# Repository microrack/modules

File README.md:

# Modules

MICRORACK modules are compact synthesizer building blocks following the [MICRORACK Specification](https://specs.microrack.org/).

> **Open Platform**
>
> Any enthusiast or brand can create and distribute compatible modules — as open source projects or as closed source designs.

## Generators

- [**oscillator**](mod-vco/) - Voltage Controlled Oscillator with LFO mode
- [**noise + s&h**](mod-noise/) - Noise Generator with Sample/Track & Hold
- [**envelope**](mod-env/) - Envelope Generator
- [**sequencer**](mod-seq/) - 4-Step Sequencer

## Sound Processing

- [**filter**](mod-vcf/) - Voltage Controlled Filter
- [**delay**](mod-delay/) - Wild  PT Delay
- [**equalizer**](mod-eq/) - 3 Line Equalizer
- [**compressor**](mod-comp/) - Compressor wit Sidechain
- [**saturator**](mod-sat/) - Saturator / Distortion
- [**lowpass gate**](mod-lpg/) - Low Pass Gate

## Utilities

- [**vca mixer**](mod-vca/) - VCA Mixer
- [**counter**](mod-clk/) - Clock Counter
- [**stylo**](mod-key/) - Stylus Keyboard

## I/O & MIDI

- [**input 6.3**](mod-in-63/) - 6.3mm jack Input
- [**output 3.5**](mod-out-35/) - 3.5mm jack Output
- [**output 6.3**](mod-out-63/) - 6.3mm jack Output
- [**midi→cv**](mod-midi/) - MIDI-CV Interface wi Osciloscope mode
- [**jacket 3.5**](mod-jacket/) - 3.5mm Jacks for Eurorack and more

## Power & Chassis

- [**power**](mod-pwr/) - Power Module
- [**rack chassis**](mod-chassis/) - Eurorack/Standalone Chassis

## Additional Resources

> **Source Repository**
>
> [github.com/microrack/modules](https://github.com/microrack/modules)

- [Documentation](https://docs.microrack.org) - User guides and documentation
- [Specification](https://specs.microrack.org) - Technical specifications
- [Forum](https://forum.microrack.org) - Community discussions

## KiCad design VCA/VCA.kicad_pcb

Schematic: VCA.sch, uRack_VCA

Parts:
C1, C2: 0.1 uF; c0603
J1: Output; pls1x03
J2: Input; pls1x03
J3: Env; pls1x03
J4, J5, J6, J7, J8, J9, J10, J11, J12: Conn_01x05_Male; pls1x05
Q1, Q2, Q3, Q4: BC817; SOT-23
Q5: BC807; SOT-23
R1, R5, R7, R10, R11, R16, R18, R19: 100K; r0603
R2, R3, R9, R17: 24K; r0603
R4, R6, R8, R15: 100R; r0603
R12, R13, R14, R20, R21, R22: 1K; r0603
RV1, RV2: 10K; R0904N
U1: LM324; soic-14

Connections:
+5V: C1.2, J4.1, J4.2, J4.3, J4.4, J4.5, J5.1, J5.2, J5.3, J5.4, J5.5, J6.1, J6.2, J6.3, J6.4, J6.5, R2.1, R3.1, U1.4 (V+)
-5V: C2.1, J9.1, J9.2, J9.3, J9.4, J9.5, J11.1, J11.2, J11.3, J11.4, J11.5, J12.1, J12.2, J12.3, J12.4, J12.5, Q3.2 (E), Q4.2 (E), U1.11 (V-)
/ENV_1: J3.1, R16.2, R20.1
/ENV_2: J3.2, R18.2, R21.1
/ENV_3: J3.3, R19.2, R22.1
/IN_2: J2.2, R7.2, R13.1
/IN_3: J2.3, R10.2, R12.1
GNDREF: C1.1, C2.2, J7.1, J7.2, J7.3, J7.4, J7.5, J8.1, J8.2, J8.3, J8.4, J8.5, J10.1, J10.2, J10.3, J10.4, J10.5, Q2.1 (B), Q5.1 (B), R11.2, R12.2, R13.2, R14.2, R15.2, R20.2, R21.2, R22.2, RV1.1, RV2.1
unnamed: J1.1, R4.1
unnamed: J1.2, R6.1
unnamed: J1.3, R8.1
unnamed: J2.1, R5.2, R14.1
unnamed: Q1.1 (B), R9.1, R15.1
unnamed: Q1.2 (E), Q2.2 (E), Q3.3 (C)
unnamed: Q1.3 (C), R1.2, R2.2, U1.6 (-)
unnamed: Q2.3 (C), R3.2, R11.1, U1.5 (+)
unnamed: Q3.1 (B), Q4.1 (B), Q4.3 (C), Q5.3 (C)
unnamed: Q5.2 (E), R17.1
unnamed: R1.1, R4.2, R6.2, R8.2, U1.7
unnamed: R9.2, RV1.3, U1.1
unnamed: R5.1, R7.1, R10.1, U1.3 (+)
unnamed: R16.1, R18.1, R19.1, U1.10 (+)
unnamed: R17.2, RV2.3, U1.8
unnamed: RV1.2, U1.2 (-)
unnamed: RV2.2, U1.9 (-)

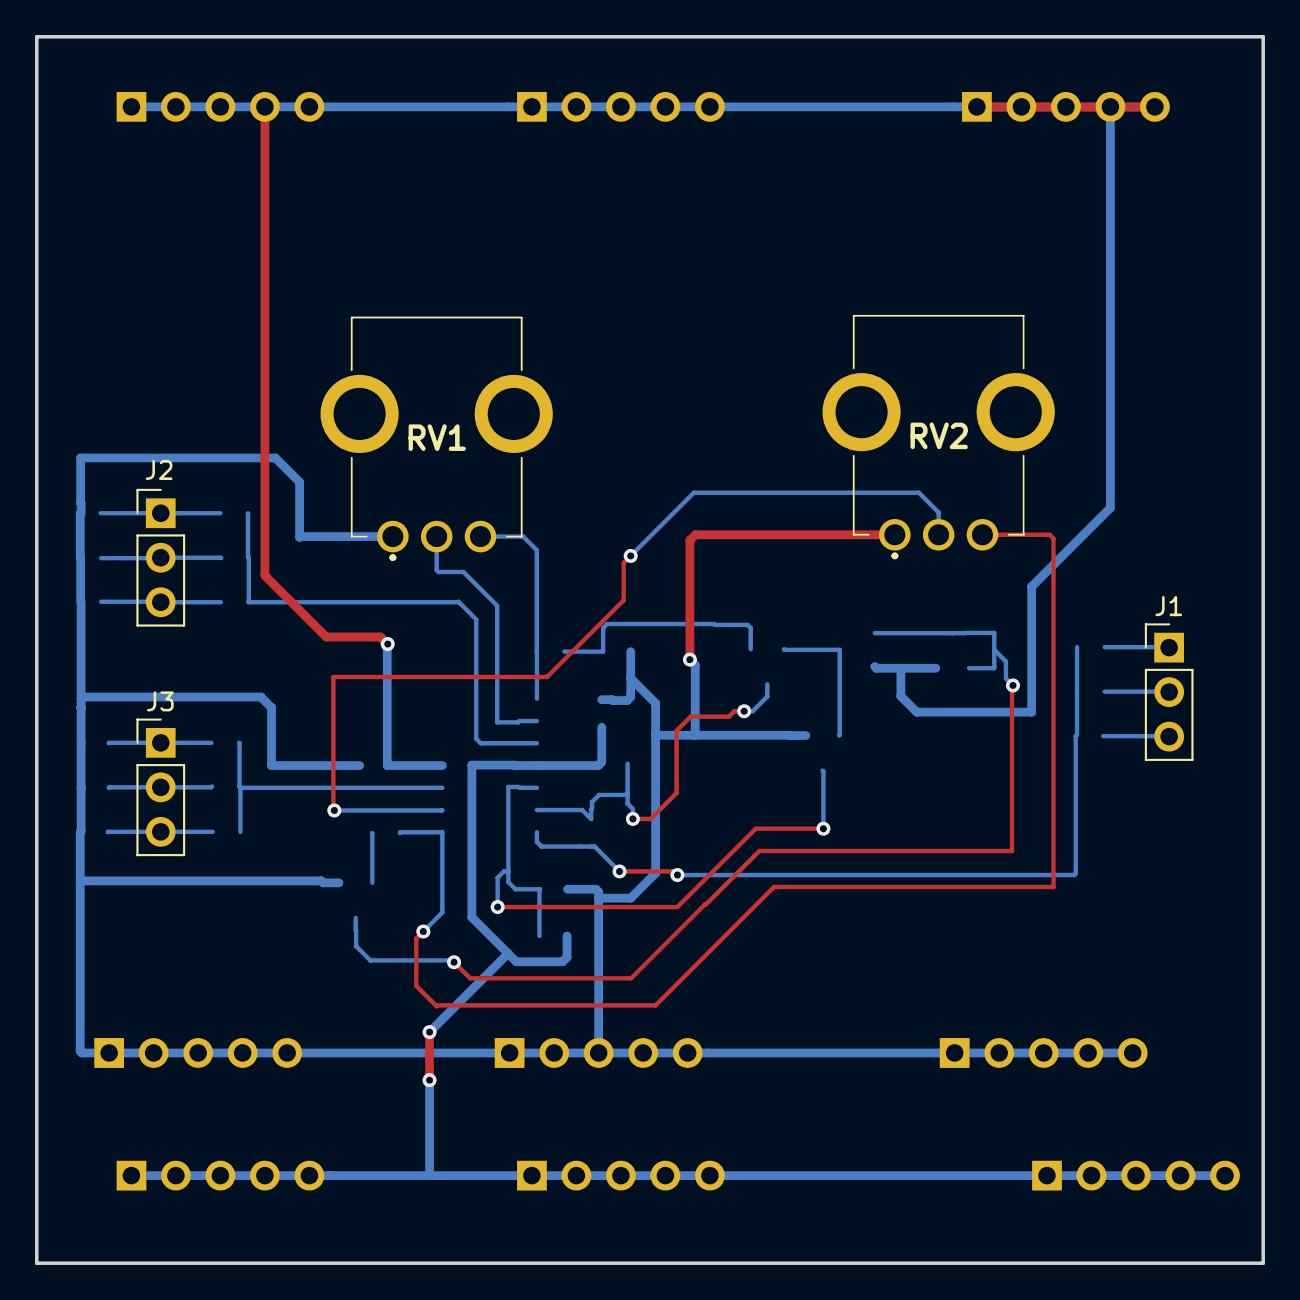
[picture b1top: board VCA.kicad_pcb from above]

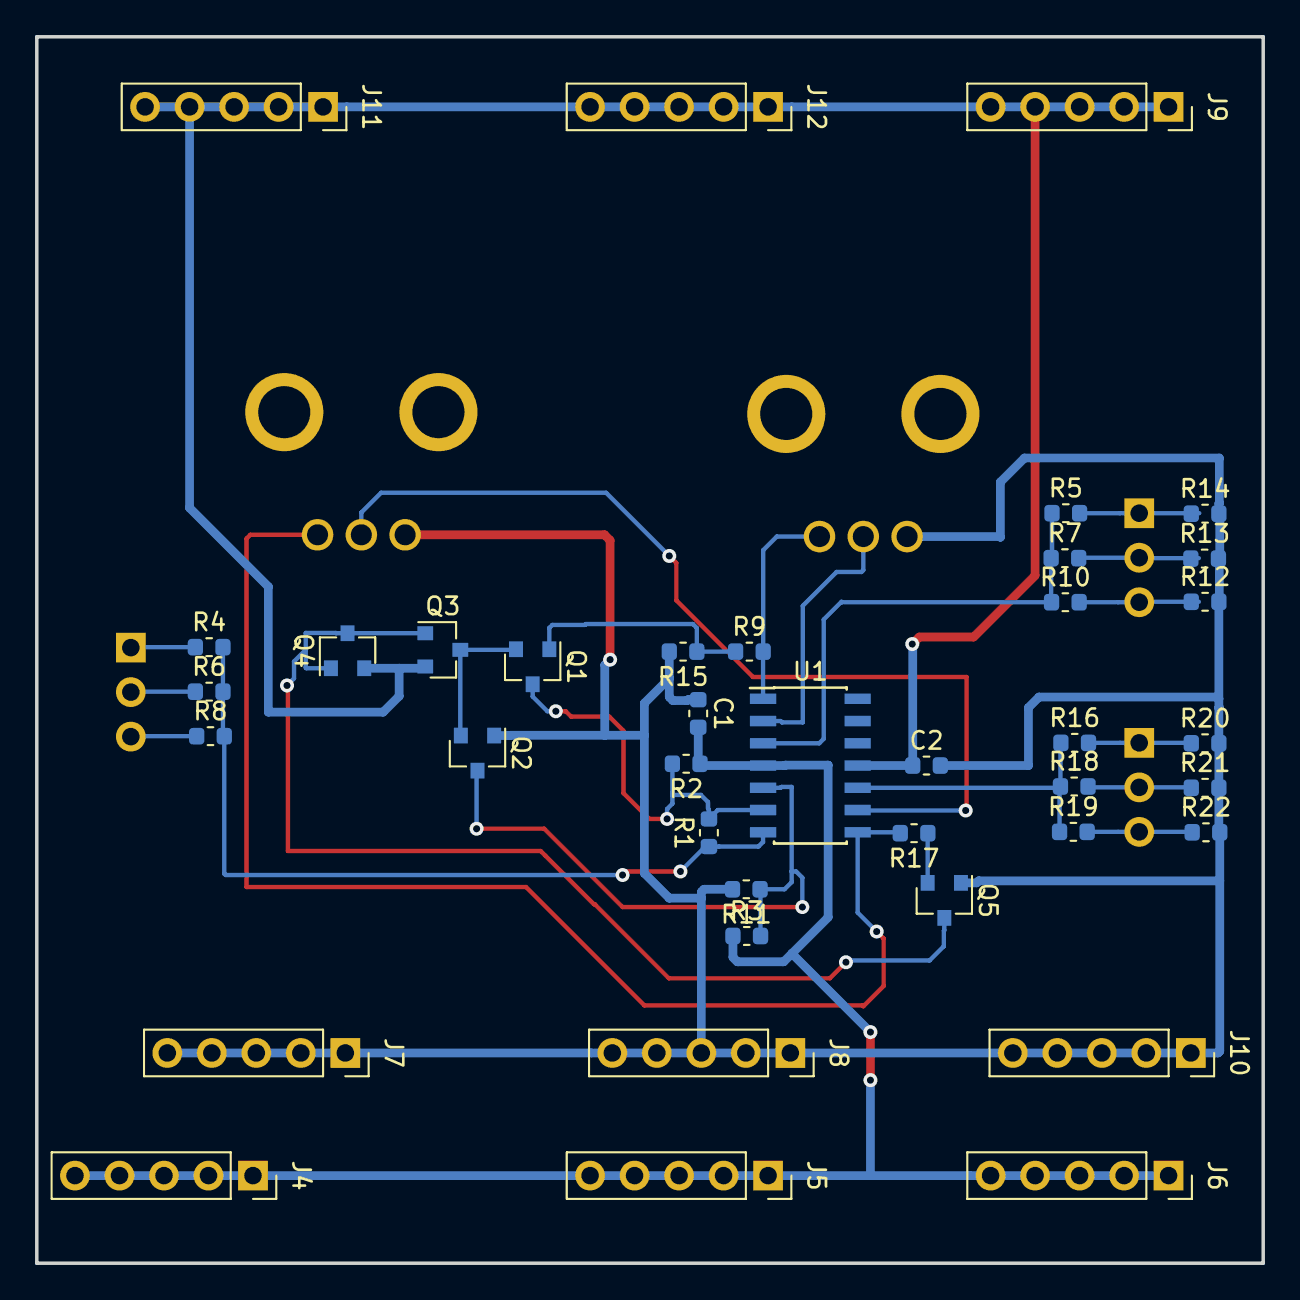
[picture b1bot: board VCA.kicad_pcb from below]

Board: 2 copper layers, 70.0 x 70.0 mm, 44 parts (39 on the bottom side), 25 nets.

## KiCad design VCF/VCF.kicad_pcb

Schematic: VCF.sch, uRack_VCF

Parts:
C1, C2, C3, C4: 0.1 uF; c0603
D1: D; d0603
J1, J2, J4, J5, J6, J7, J8, J10, J12: Conn_01x05_Male; pls1x05
J3: Env; pls1x02
J9: Output; pls1x03
J11: Input; pls1x02
R1, R2, R4, R10, R11: 10K; r0603
R3, R5, R6, R9, R16, R18: 100K; r0603
R7, R8, R19, R20: 1K; r0603
R12, R14, R17: 100R; r0603
R13, R15: 24K; r0603
RV1, RV2, RV3: 10K; R0904N
U1: LM324A; soic-14

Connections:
+5V: C1.2, J1.1, J1.2, J1.3, J1.4, J1.5, J2.1, J2.2, J2.3, J2.4, J2.5, J4.1, J4.2, J4.3, J4.4, J4.5, RV2.1, U1.4 (V+)
-5V: C2.2, J8.1, J8.2, J8.3, J8.4, J8.5, J10.1, J10.2, J10.3, J10.4, J10.5, J12.1, J12.2, J12.3, J12.4, J12.5, RV2.3, U1.11 (V-)
/ENV_2: J3.1, J3.2, R3.2, R5.2, R7.1, R8.1
/IN_2: J11.2, R18.2, R20.1
/OUT_1: J9.1, R12.1
/OUT_2: J9.2, R14.1
GNDREF: C1.1, C2.1, D1.1 (K), J5.1, J5.2, J5.3, J5.4, J5.5, J6.1, J6.2, J6.3, J6.4, J6.5, J7.1, J7.2, J7.3, J7.4, J7.5, R1.2, R7.2, R8.2, R10.2, R19.2, R20.2, RV1.1, U1.12 (+)
unnamed: C3.1, C4.2, D1.2 (A), R4.1
unnamed: C3.2, R13.2, R15.1, U1.13 (-)
unnamed: C4.1, RV3.1
unnamed: J9.3, R17.1
unnamed: J11.1, R16.2, R19.1
unnamed: R1.1, R2.2, U1.6 (-)
unnamed: R2.1, R4.2, U1.7
unnamed: R3.1, R5.1, U1.3 (+)
unnamed: R6.1, R9.1, U1.5 (+)
unnamed: R6.2, RV1.3, U1.1
unnamed: R9.2, RV2.2
unnamed: R10.1, R11.2, U1.9 (-)
unnamed: R11.1, R15.2, U1.8
unnamed: R12.2, R13.1, R14.2, R17.2, RV3.2, RV3.3, U1.14
unnamed: R16.1, R18.1, U1.10 (+)
unnamed: RV1.2, U1.2 (-)

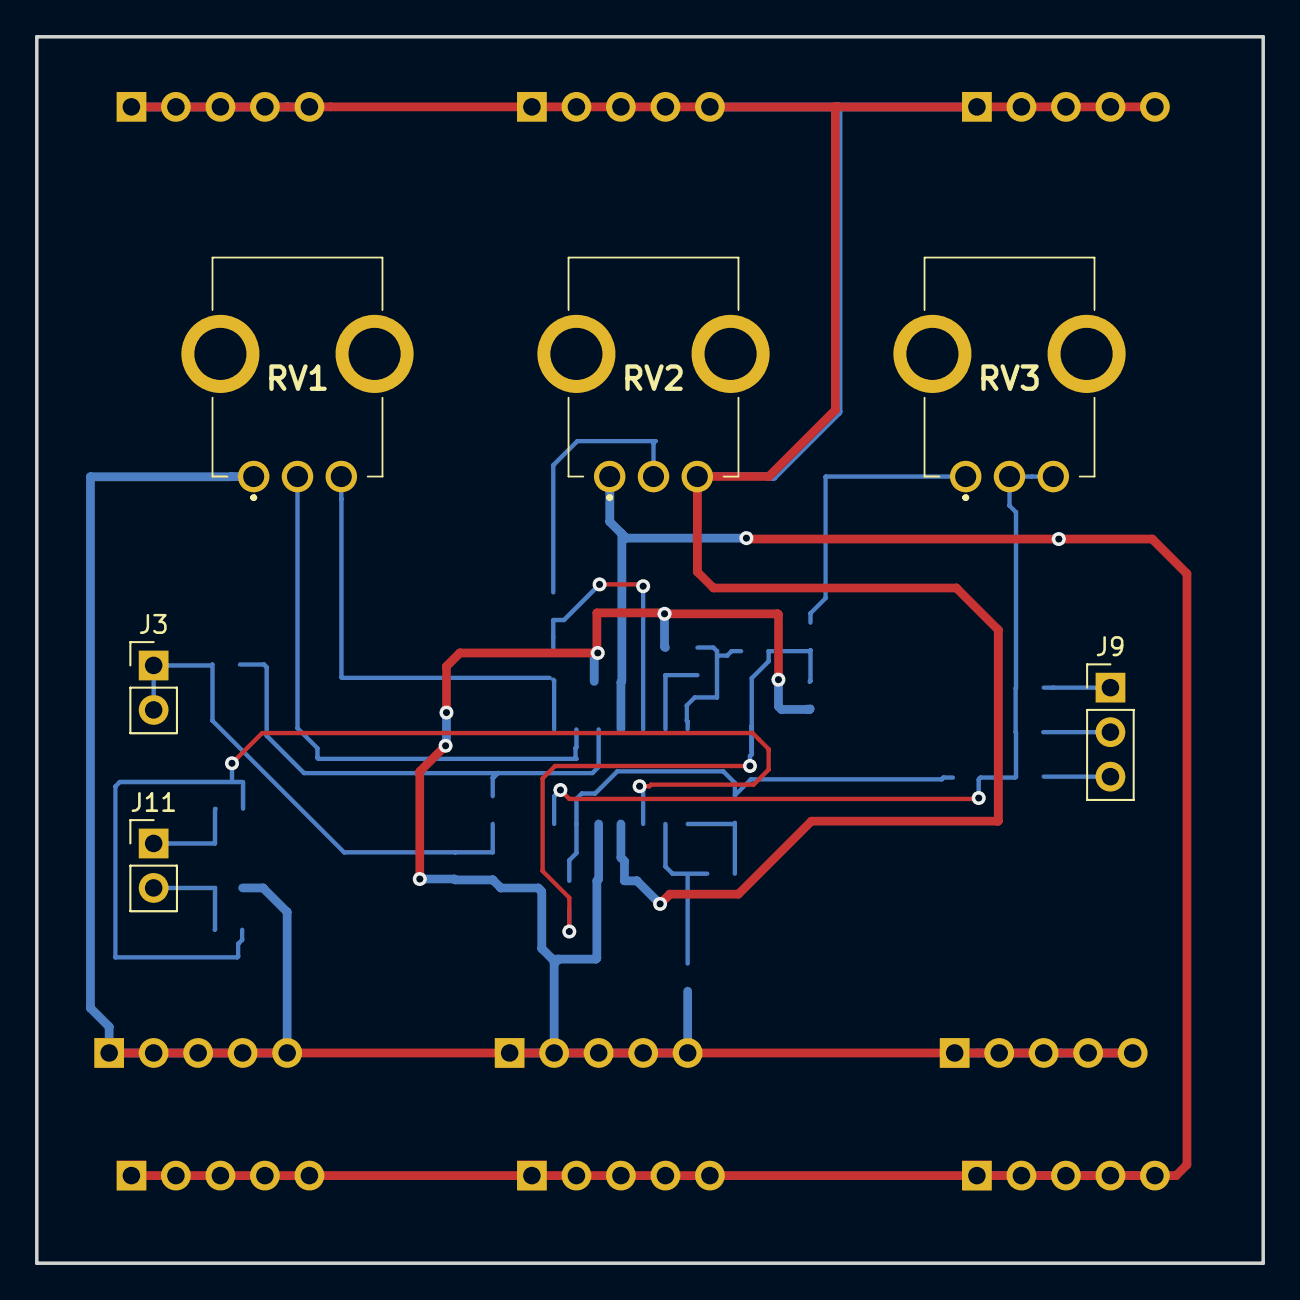
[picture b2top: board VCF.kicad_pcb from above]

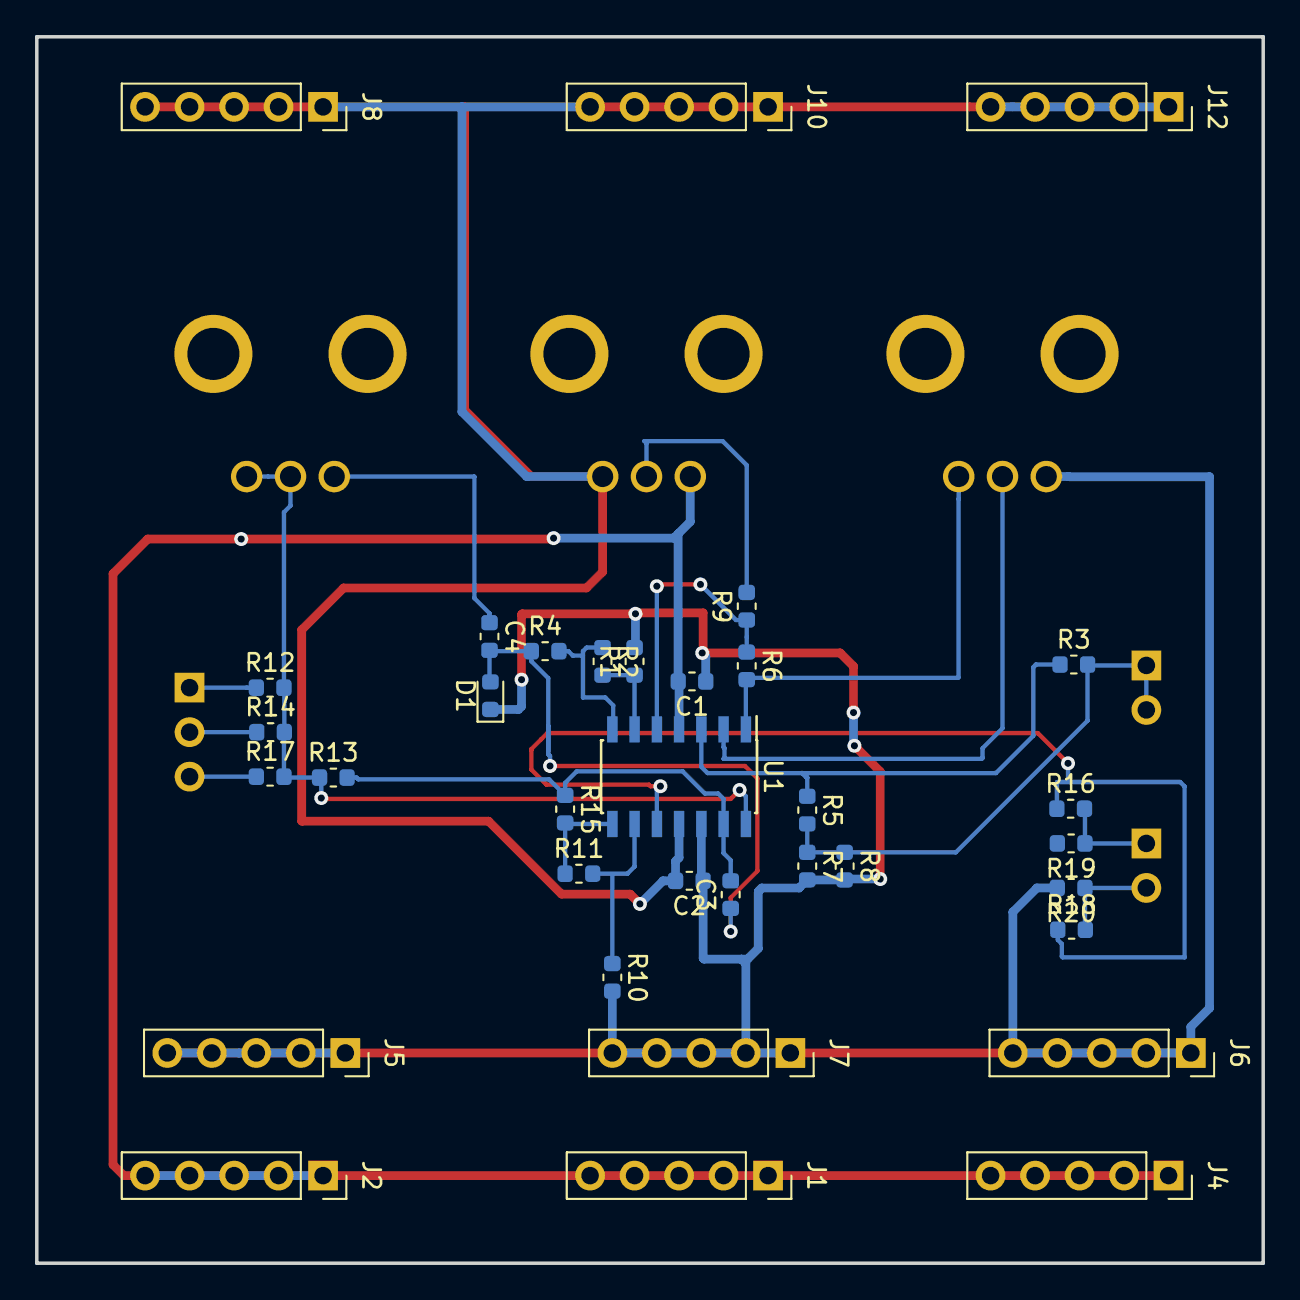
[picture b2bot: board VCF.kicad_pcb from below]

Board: 2 copper layers, 70.0 x 70.0 mm, 41 parts (35 on the bottom side), 23 nets.

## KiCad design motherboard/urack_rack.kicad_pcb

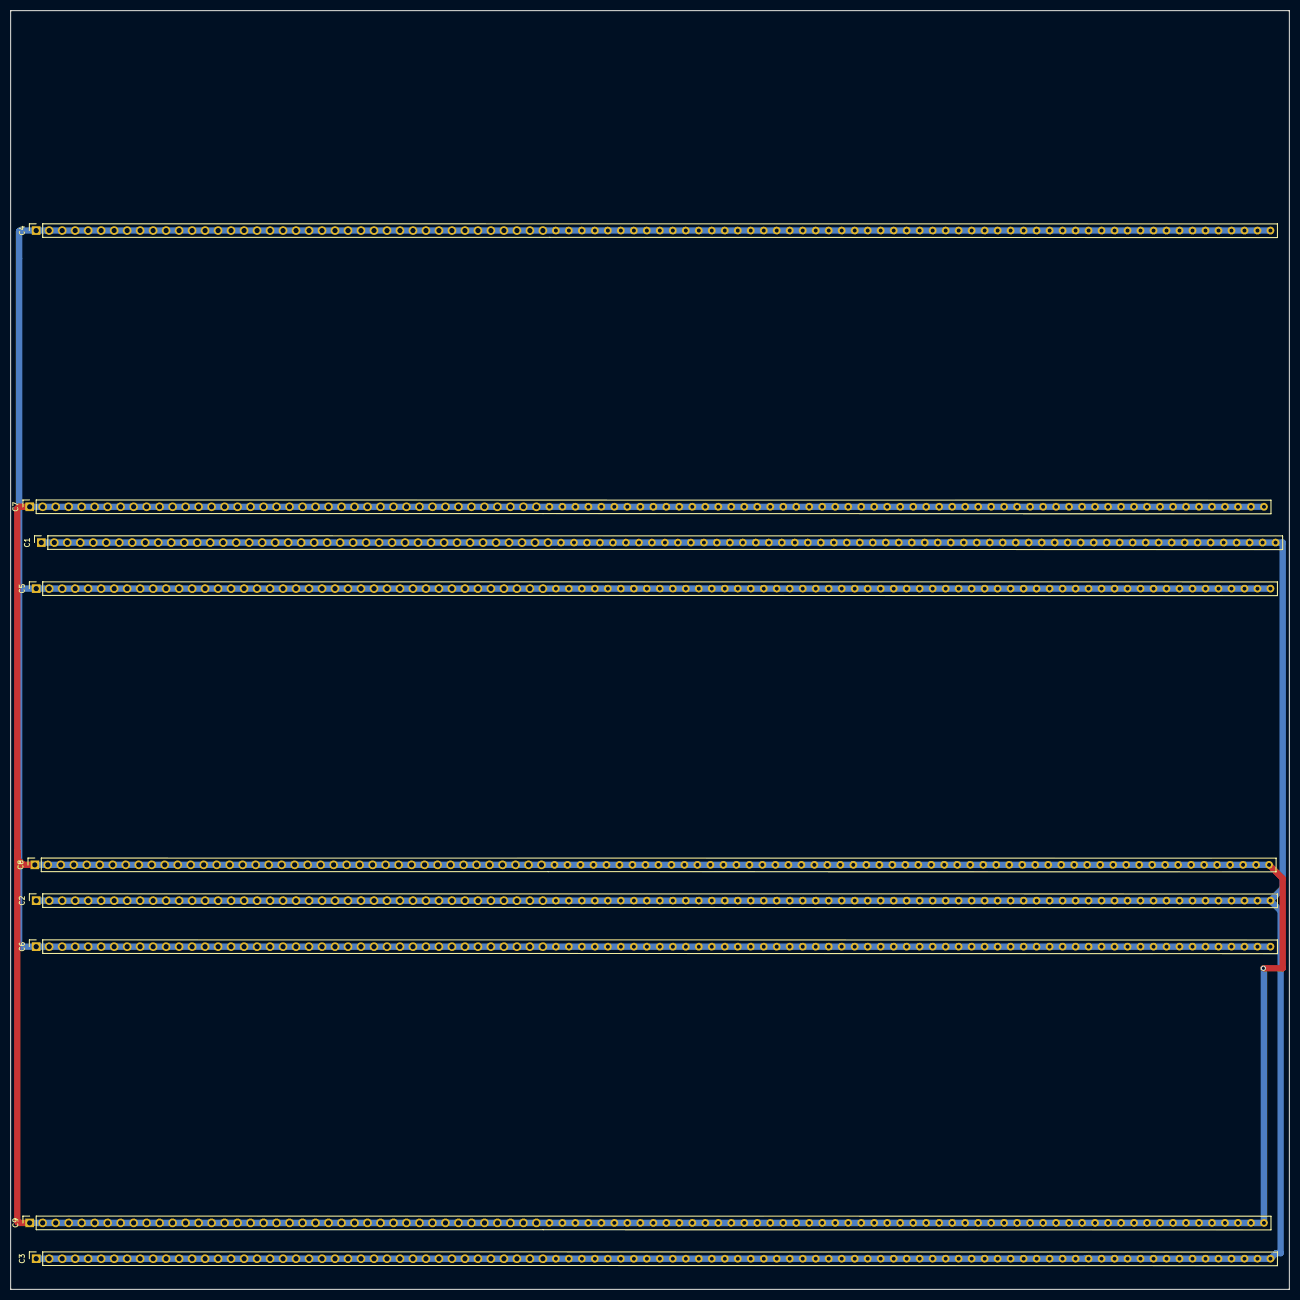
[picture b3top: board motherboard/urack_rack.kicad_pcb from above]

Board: 2 copper layers, 250.0 x 250.0 mm, 9 parts (0 on the bottom side), 3 nets.

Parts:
C1, C2, C3, C4, C5, C6, C7, C8, C9: Conn_01x96_Female; pbd1x96

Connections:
+5V: C1.1, C1.2, C1.3, C1.4, C1.5, C1.6, C1.7, C1.8, C1.9, C1.10, C1.11, C1.12, C1.13, C1.14, C1.15, C1.16, C1.17, C1.18, C1.19, C1.20, C1.21, C1.22, C1.23, C1.24, C1.25, C1.26, C1.27, C1.28, C1.29, C1.30, C1.31, C1.32, C1.33, C1.34, C1.35, C1.36, C1.37, C1.38, C1.39, C1.40, C1.41, C1.42, C1.43, C1.44, C1.45, C1.46, C1.47, C1.48, C1.49, C1.50, C1.51, C1.52, C1.53, C1.54, C1.55, C1.56, C1.57, C1.58, C1.59, C1.60, C1.61, C1.62, C1.63, C1.64, C1.65, C1.66, C1.67, C1.68, C1.69, C1.70, C1.71, C1.72, C1.73, C1.74, C1.75, C1.76, C1.77, C1.78, C1.79, C1.80, C1.81, C1.82, C1.83, C1.84, C1.85, C1.86, C1.87, C1.88, C1.89, C1.90, C1.91, C1.92, C1.93, C1.94, C1.95, C1.96, C2.1, C2.2, C2.3, C2.4, C2.5, C2.6, C2.7, C2.8, C2.9, C2.10, C2.11, C2.12, C2.13, C2.14, C2.15, C2.16, C2.17, C2.18, C2.19, C2.20, C2.21, C2.22, C2.23, C2.24, C2.25, C2.26, C2.27, C2.28, C2.29, C2.30, C2.31, C2.32, C2.33, C2.34, C2.35, C2.36, C2.37, C2.38, C2.39, C2.40, C2.41, C2.42, C2.43, C2.44, C2.45, C2.46, C2.47, C2.48, C2.49, C2.50, C2.51, C2.52, C2.53, C2.54, C2.55, C2.56, C2.57, C2.58, C2.59, C2.60, C2.61, C2.62, C2.63, C2.64, C2.65, C2.66, C2.67, C2.68, C2.69, C2.70, C2.71, C2.72, C2.73, C2.74, C2.75, C2.76, C2.77, C2.78, C2.79, C2.80, C2.81, C2.82, C2.83, C2.84, C2.85, C2.86, C2.87, C2.88, C2.89, C2.90, C2.91, C2.92, C2.93, C2.94, C2.95, C2.96, C3.1, C3.2, C3.3, C3.4, C3.5, C3.6, C3.7, C3.8, C3.9, C3.10, C3.11, C3.12, C3.13, C3.14, C3.15, C3.16, C3.17, C3.18, C3.19, C3.20, C3.21, C3.22, C3.23, C3.24, C3.25, C3.26, C3.27, C3.28, C3.29, C3.30, C3.31, C3.32, C3.33, C3.34, C3.35, C3.36, C3.37, C3.38, C3.39, C3.40, C3.41, C3.42, C3.43, C3.44, C3.45, C3.46, C3.47, C3.48, C3.49, C3.50, C3.51, C3.52, C3.53, C3.54, C3.55, C3.56, C3.57, C3.58, C3.59, C3.60, C3.61, C3.62, C3.63, C3.64, C3.65, C3.66, C3.67, C3.68, C3.69, C3.70, C3.71, C3.72, C3.73, C3.74, C3.75, C3.76, C3.77, C3.78, C3.79, C3.80, C3.81, C3.82, C3.83, C3.84, C3.85, C3.86, C3.87, C3.88, C3.89, C3.90, C3.91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
-5V: C4.1, C4.2, C4.3, C4.4, C4.5, C4.6, C4.7, C4.8, C4.9, C4.10, C4.11, C4.12, C4.13, C4.14, C4.15, C4.16, C4.17, C4.18, C4.19, C4.20, C4.21, C4.22, C4.23, C4.24, C4.25, C4.26, C4.27, C4.28, C4.29, C4.30, C4.31, C4.32, C4.33, C4.34, C4.35, C4.36, C4.37, C4.38, C4.39, C4.40, C4.41, C4.42, C4.43, C4.44, C4.45, C4.46, C4.47, C4.48, C4.49, C4.50, C4.51, C4.52, C4.53, C4.54, C4.55, C4.56, C4.57, C4.58, C4.59, C4.60, C4.61, C4.62, C4.63, C4.64, C4.65, C4.66, C4.67, C4.68, C4.69, C4.70, C4.71, C4.72, C4.73, C4.74, C4.75, C4.76, C4.77, C4.78, C4.79, C4.80, C4.81, C4.82, C4.83, C4.84, C4.85, C4.86, C4.87, C4.88, C4.89, C4.90, C4.91, C4.92, C4.93, C4.94, C4.95, C4.96, C5.1, C5.2, C5.3, C5.4, C5.5, C5.6, C5.7, C5.8, C5.9, C5.10, C5.11, C5.12, C5.13, C5.14, C5.15, C5.16, C5.17, C5.18, C5.19, C5.20, C5.21, C5.22, C5.23, C5.24, C5.25, C5.26, C5.27, C5.28, C5.29, C5.30, C5.31, C5.32, C5.33, C5.34, C5.35, C5.36, C5.37, C5.38, C5.39, C5.40, C5.41, C5.42, C5.43, C5.44, C5.45, C5.46, C5.47, C5.48, C5.49, C5.50, C5.51, C5.52, C5.53, C5.54, C5.55, C5.56, C5.57, C5.58, C5.59, C5.60, C5.61, C5.62, C5.63, C5.64, C5.65, C5.66, C5.67, C5.68, C5.69, C5.70, C5.71, C5.72, C5.73, C5.74, C5.75, C5.76, C5.77, C5.78, C5.79, C5.80, C5.81, C5.82, C5.83, C5.84, C5.85, C5.86, C5.87, C5.88, C5.89, C5.90, C5.91, C5.92, C5.93, C5.94, C5.95, C5.96, C6.1, C6.2, C6.3, C6.4, C6.5, C6.6, C6.7, C6.8, C6.9, C6.10, C6.11, C6.12, C6.13, C6.14, C6.15, C6.16, C6.17, C6.18, C6.19, C6.20, C6.21, C6.22, C6.23, C6.24, C6.25, C6.26, C6.27, C6.28, C6.29, C6.30, C6.31, C6.32, C6.33, C6.34, C6.35, C6.36, C6.37, C6.38, C6.39, C6.40, C6.41, C6.42, C6.43, C6.44, C6.45, C6.46, C6.47, C6.48, C6.49, C6.50, C6.51, C6.52, C6.53, C6.54, C6.55, C6.56, C6.57, C6.58, C6.59, C6.60, C6.61, C6.62, C6.63, C6.64, C6.65, C6.66, C6.67, C6.68, C6.69, C6.70, C6.71, C6.72, C6.73, C6.74, C6.75, C6.76, C6.77, C6.78, C6.79, C6.80, C6.81, C6.82, C6.83, C6.84, C6.85, C6.86, C6.87, C6.88, C6.89, C6.90, C6.91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
GNDREF: C7.1, C7.2, C7.3, C7.4, C7.5, C7.6, C7.7, C7.8, C7.9, C7.10, C7.11, C7.12, C7.13, C7.14, C7.15, C7.16, C7.17, C7.18, C7.19, C7.20, C7.21, C7.22, C7.23, C7.24, C7.25, C7.26, C7.27, C7.28, C7.29, C7.30, C7.31, C7.32, C7.33, C7.34, C7.35, C7.36, C7.37, C7.38, C7.39, C7.40, C7.41, C7.42, C7.43, C7.44, C7.45, C7.46, C7.47, C7.48, C7.49, C7.50, C7.51, C7.52, C7.53, C7.54, C7.55, C7.56, C7.57, C7.58, C7.59, C7.60, C7.61, C7.62, C7.63, C7.64, C7.65, C7.66, C7.67, C7.68, C7.69, C7.70, C7.71, C7.72, C7.73, C7.74, C7.75, C7.76, C7.77, C7.78, C7.79, C7.80, C7.81, C7.82, C7.83, C7.84, C7.85, C7.86, C7.87, C7.88, C7.89, C7.90, C7.91, C7.92, C7.93, C7.94, C7.95, C7.96, C8.1, C8.2, C8.3, C8.4, C8.5, C8.6, C8.7, C8.8, C8.9, C8.10, C8.11, C8.12, C8.13, C8.14, C8.15, C8.16, C8.17, C8.18, C8.19, C8.20, C8.21, C8.22, C8.23, C8.24, C8.25, C8.26, C8.27, C8.28, C8.29, C8.30, C8.31, C8.32, C8.33, C8.34, C8.35, C8.36, C8.37, C8.38, C8.39, C8.40, C8.41, C8.42, C8.43, C8.44, C8.45, C8.46, C8.47, C8.48, C8.49, C8.50, C8.51, C8.52, C8.53, C8.54, C8.55, C8.56, C8.57, C8.58, C8.59, C8.60, C8.61, C8.62, C8.63, C8.64, C8.65, C8.66, C8.67, C8.68, C8.69, C8.70, C8.71, C8.72, C8.73, C8.74, C8.75, C8.76, C8.77, C8.78, C8.79, C8.80, C8.81, C8.82, C8.83, C8.84, C8.85, C8.86, C8.87, C8.88, C8.89, C8.90, C8.91, C8.92, C8.93, C8.94, C8.95, C8.96, C9.1, C9.2, C9.3, C9.4, C9.5, C9.6, C9.7, C9.8, C9.9, C9.10, C9.11, C9.12, C9.13, C9.14, C9.15, C9.16, C9.17, C9.18, C9.19, C9.20, C9.21, C9.22, C9.23, C9.24, C9.25, C9.26, C9.27, C9.28, C9.29, C9.30, C9.31, C9.32, C9.33, C9.34, C9.35, C9.36, C9.37, C9.38, C9.39, C9.40, C9.41, C9.42, C9.43, C9.44, C9.45, C9.46, C9.47, C9.48, C9.49, C9.50, C9.51, C9.52, C9.53, C9.54, C9.55, C9.56, C9.57, C9.58, C9.59, C9.60, C9.61, C9.62, C9.63, C9.64, C9.65, C9.66, C9.67, C9.68, C9.69, C9.70, C9.71, C9.72, C9.73, C9.74, C9.75, C9.76, C9.77, C9.78, C9.79, C9.80, C9.81, C9.82, C9.83, C9.84, C9.85, C9.86, C9.87, C9.88, C9.89, C9.90, C9.91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

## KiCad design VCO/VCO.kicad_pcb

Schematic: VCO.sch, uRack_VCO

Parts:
C1, C2, C4, C5: 0.1 uF; c0603
C3: 1 nF; c0603
C6: 10 nF; c0603
J1, J2, J4, J5, J6, J7, J8, J9, J11: Conn_01x05_Male; pls1x05
J3: Input; pls1x03
J10: Output; pls1x02
J12: PW; pls1x01
Q1, Q2, Q3: BC807; SOT-23
R1: 1M; r0603
R2, R10, R12, R14, R15, R18, R19, R22: 24K; r0603
R3, R4, R5, R21, R23: 100K; r0603
R6, R7, R8, R9, R17, R24: 1K; r0603
R11, R13: 100R; r0603
R16, R20: 10K; r0603
RV1, RV2: 10K; w3296w
RV3, RV4, RV5: 10K; PTV09A4020FB103
S1: Switch; smts; Manufacturer_Part_Number M2013SS1W03; Mouser Part Number 633-M201303
U1, U2: LM324A; soic-14

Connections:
+5V: C1.2, C2.2, J1.1, J1.2, J1.3, J1.4, J1.5, J2.1, J2.2, J2.3, J2.4, J2.5, J4.1, J4.2, J4.3, J4.4, J4.5, R1.1, R16.1, RV3.1, RV5.1, U1.4 (V+), U2.4 (V+)
-5V: C4.1, C5.1, J8.1, J8.2, J8.3, J8.4, J8.5, J9.1, J9.2, J9.3, J9.4, J9.5, J11.1, J11.2, J11.3, J11.4, J11.5, RV3.3, RV5.3, U1.11 (V-), U2.11 (V-)
/IN_1: J3.1, R3.2, R7.1
/IN_2: J3.2, R4.2, R8.1
/IN_3: J3.3, R5.2, R9.1
/PW: J12.1, R23.2, R24.1
GNDREF: C1.1, C2.1, C4.2, C5.2, J5.1, J5.2, J5.3, J5.4, J5.5, J6.1, J6.2, J6.3, J6.4, J6.5, J7.1, J7.2, J7.3, J7.4, J7.5, Q2.1 (B), Q3.2 (E), R7.2, R8.2, R9.2, R15.2, R20.2, R24.2, RV4.3, U1.3 (+), U1.5 (+), U1.10 (+)
unnamed: C3.1, R6.2, U1.8
unnamed: C3.2, Q1.3 (C), R1.2, U1.9 (-)
unnamed: C6.1, S1.2, U1.14, U2.2 (-), U2.6 (-)
unnamed: C6.2, R12.1, R17.1, U1.13 (-)
unnamed: J10.1, R11.1
unnamed: J10.2, R13.1
unnamed: Q1.1 (B), RV1.2, RV1.3, U1.1
unnamed: Q1.2 (E), Q2.2 (E), R6.1
unnamed: Q2.3 (C), R2.2, U1.6 (-)
unnamed: Q3.1 (B), R22.2
unnamed: Q3.3 (C), R17.2
unnamed: R2.1, RV2.1, RV2.2
unnamed: R3.1, R4.1, R5.1, R10.1, RV1.1, U1.2 (-)
unnamed: R10.2, RV3.2
unnamed: R11.2, R13.2, U2.8, U2.9 (-)
unnamed: R12.2, R14.2, RV2.3, U1.7
unnamed: R14.1, R15.1, U1.12 (+)
unnamed: R16.2, R18.2, R20.1
unnamed: R18.1, R19.2, U2.3 (+)
unnamed: R19.1, R22.1, U2.1
unnamed: R21.1, R23.1, U2.5 (+)
unnamed: R21.2, RV5.2
unnamed: RV4.1, S1.3
unnamed: RV4.2, U2.10 (+)
unnamed: S1.1, U2.7

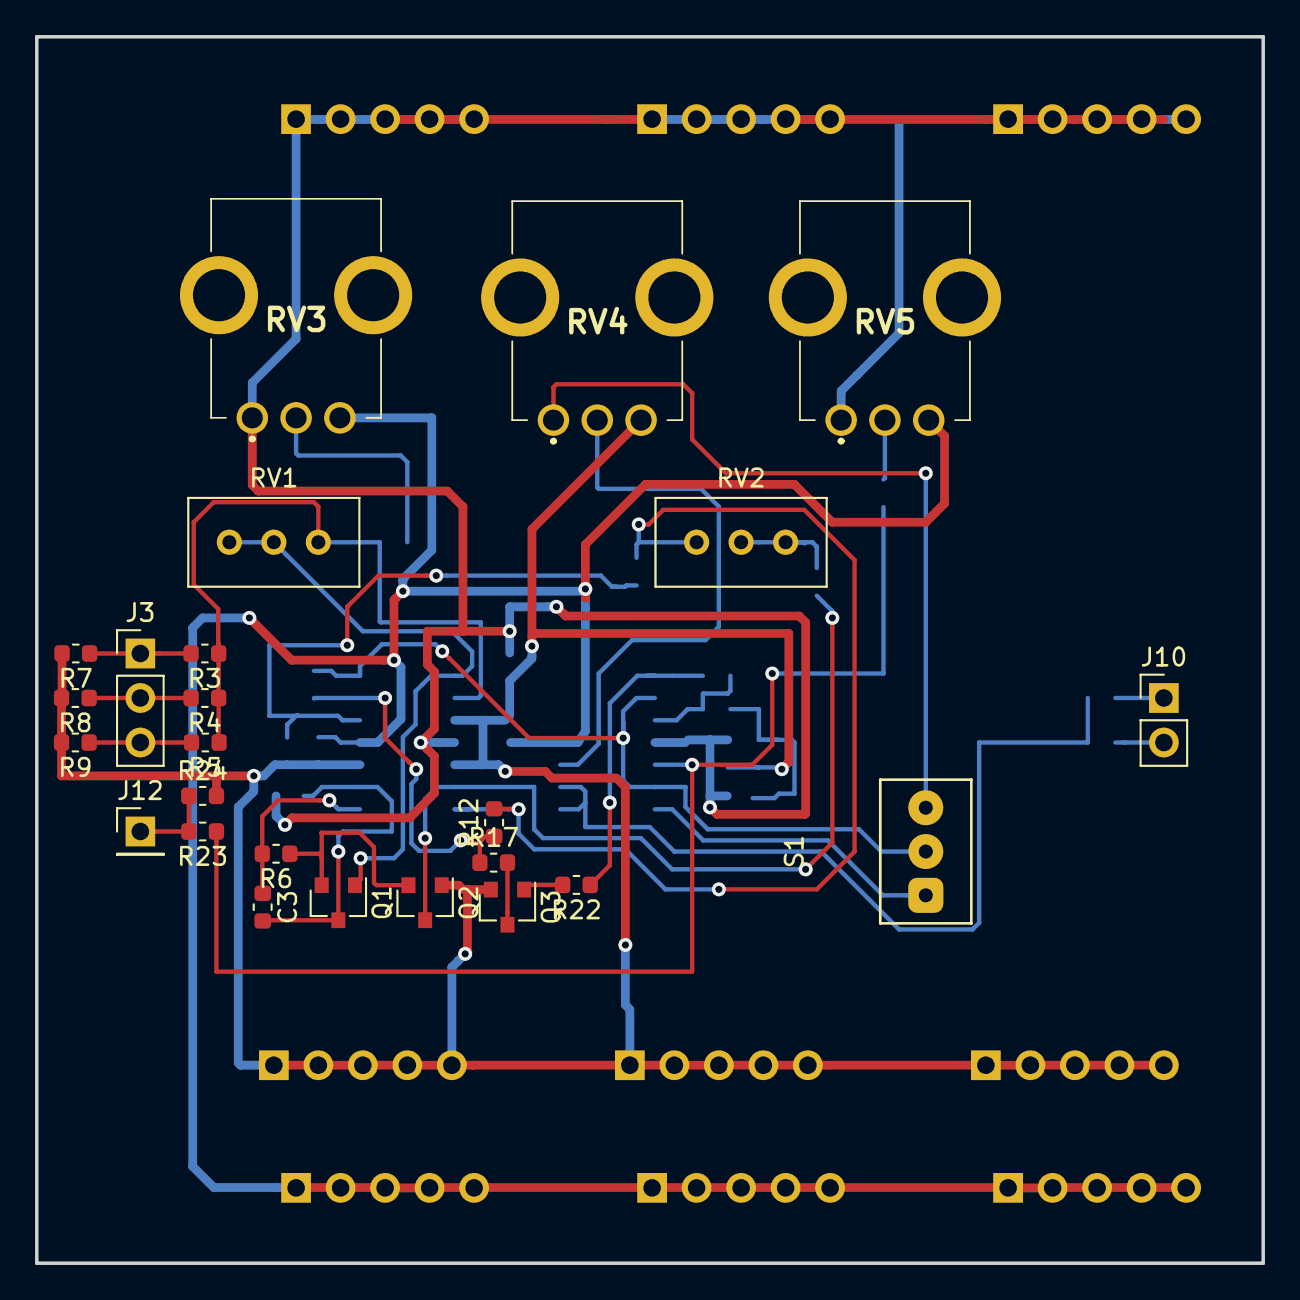
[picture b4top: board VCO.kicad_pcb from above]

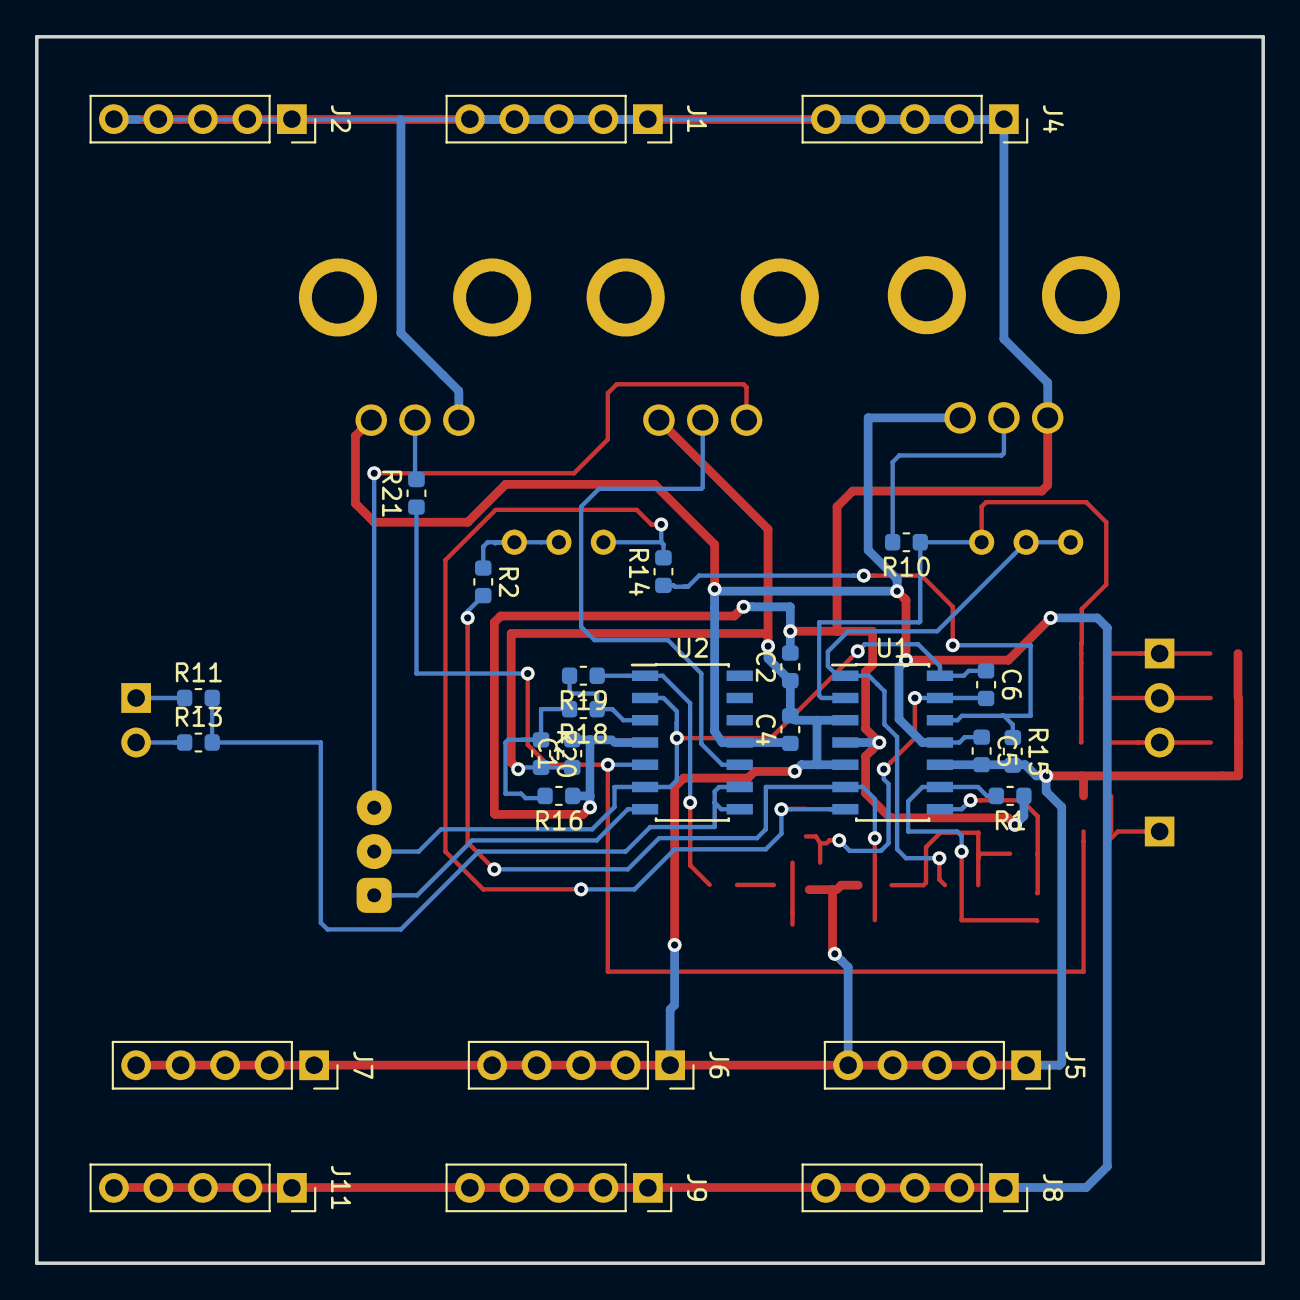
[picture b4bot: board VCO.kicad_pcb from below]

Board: 2 copper layers, 70.0 x 70.0 mm, 53 parts (28 on the bottom side), 32 nets.

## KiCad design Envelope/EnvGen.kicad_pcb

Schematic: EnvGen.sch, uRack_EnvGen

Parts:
C1, C2: 10 nF; c0603
C3: 22x25v; cp_5x2_5
C4, C5: 0.1 uF; c0603
D1, D2, D3, D4, D5, D6: D; d0603
J1: Input; pls1x02
J2: Output; pls1x03
J3, J4, J5, J6, J7, J8, J9, J10, J11: Conn_01x05_Male; pls1x05
Q1, Q2, Q3: BC817; SOT-23
R1, R2, R3, R5, R7, R9: 10K; r0603
R4, R8, R10, R11, R12, R13: 100R; r0603
R6: R; r0603
RV1, RV2, RV4: 100K; R0904N
RV3: 10K; R0904N
U1: NE555; soic-8
U2: LM324; soic-14

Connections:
+5V: C5.2, J9.1, J9.2, J9.3, J9.4, J9.5, J10.1, J10.2, J10.3, J10.4, J10.5, J11.1, J11.2, J11.3, J11.4, J11.5, R1.2, R2.1, R3.1, R5.1, U1.8, U2.11 (V-)
-5V: C4.1, J3.1, J3.2, J3.3, J3.4, J3.5, J4.1, J4.2, J4.3, J4.4, J4.5, J6.1, J6.2, J6.3, J6.4, J6.5, U2.4 (V+)
/OUT_2: J2.2, R11.2
GNDREF: C2.2, C3.2, C4.2, C5.1, D3.2, J5.1, J5.2, J5.3, J5.4, J5.5, J7.1, J7.2, J7.3, J7.4, J7.5, J8.1, J8.2, J8.3, J8.4, J8.5, Q1.2, Q2.2, Q3.2, U1.1
unnamed: C1.1, D3.1, R7.2
unnamed: C1.2, Q2.3, R3.2, RV1.1, U1.4
unnamed: C2.1, U1.5
unnamed: C3.1, R4.1, R10.1, R12.1, U1.6, U2.3 (+)
unnamed: D1.1, RV1.2, RV1.3
unnamed: D1.2, R4.2
unnamed: D2.1, D5.1, R9.2
unnamed: D2.2, J1.1
unnamed: D4.1, R10.2
unnamed: D4.2, RV2.2, RV2.3
unnamed: D5.2, J1.2
unnamed: D6.1, RV4.2, RV4.3
unnamed: D6.2, R12.2
unnamed: J2.1, R8.1
unnamed: J2.3, R13.1
unnamed: Q1.1, R9.1
unnamed: Q1.3, R2.2, R6.2
unnamed: Q2.1, R6.1
unnamed: Q3.1, R7.1
unnamed: Q3.3, R5.2, U1.2
unnamed: R1.1, RV3.1
unnamed: R8.2, R11.1, R13.2, U2.1, U2.2 (-)
unnamed: RV2.1, U1.3
unnamed: RV3.2, RV4.1
unnamed: RV3.3, U1.7

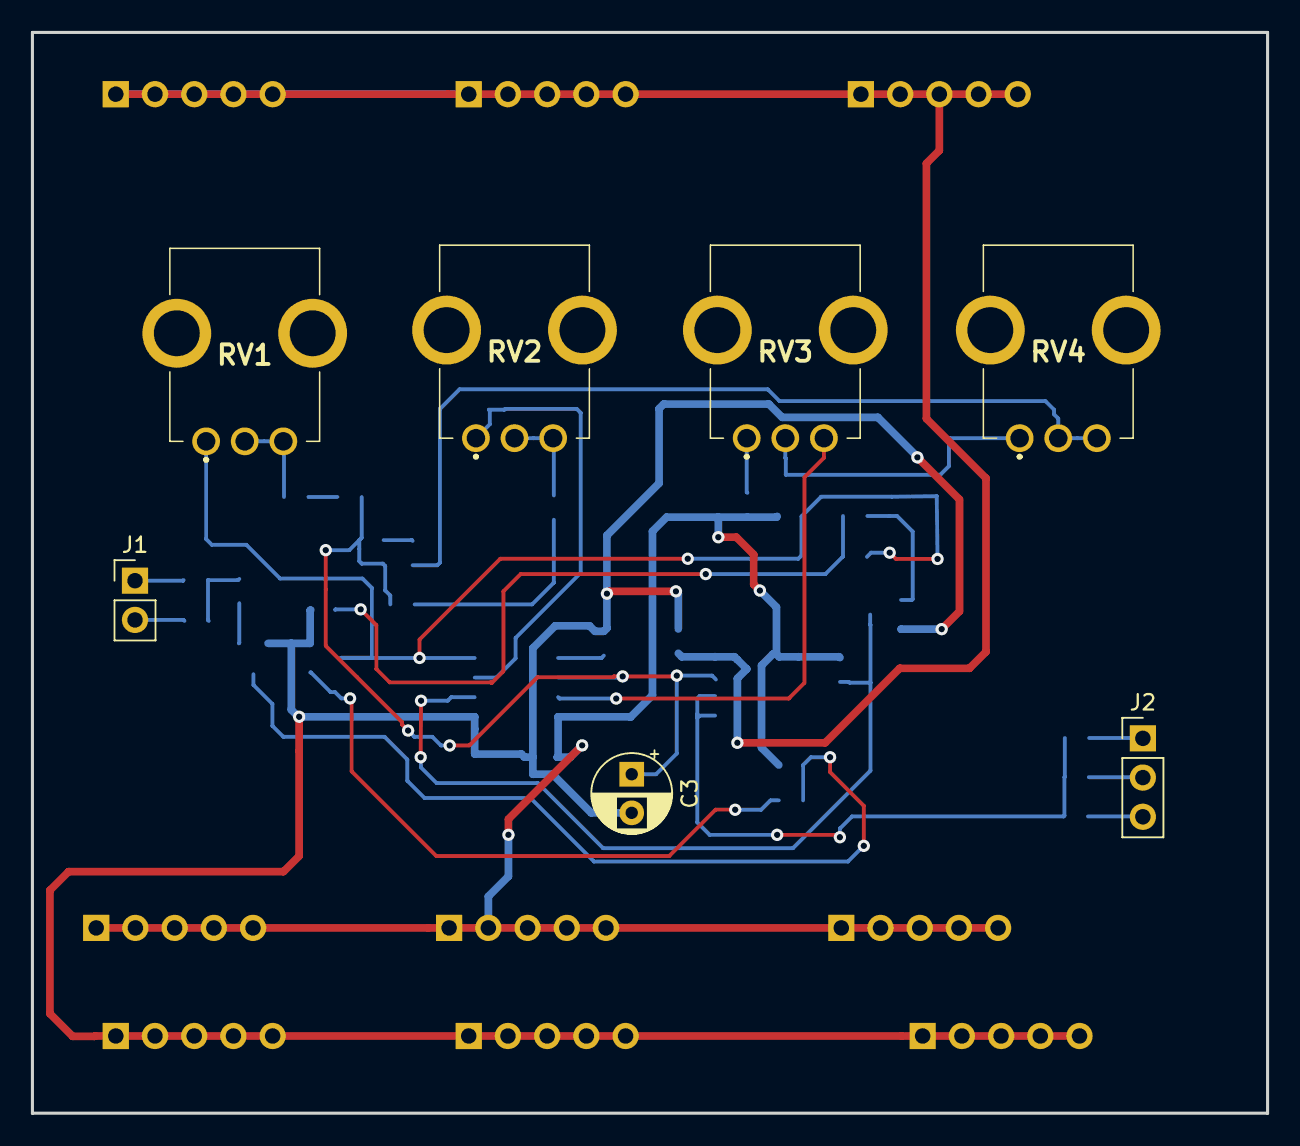
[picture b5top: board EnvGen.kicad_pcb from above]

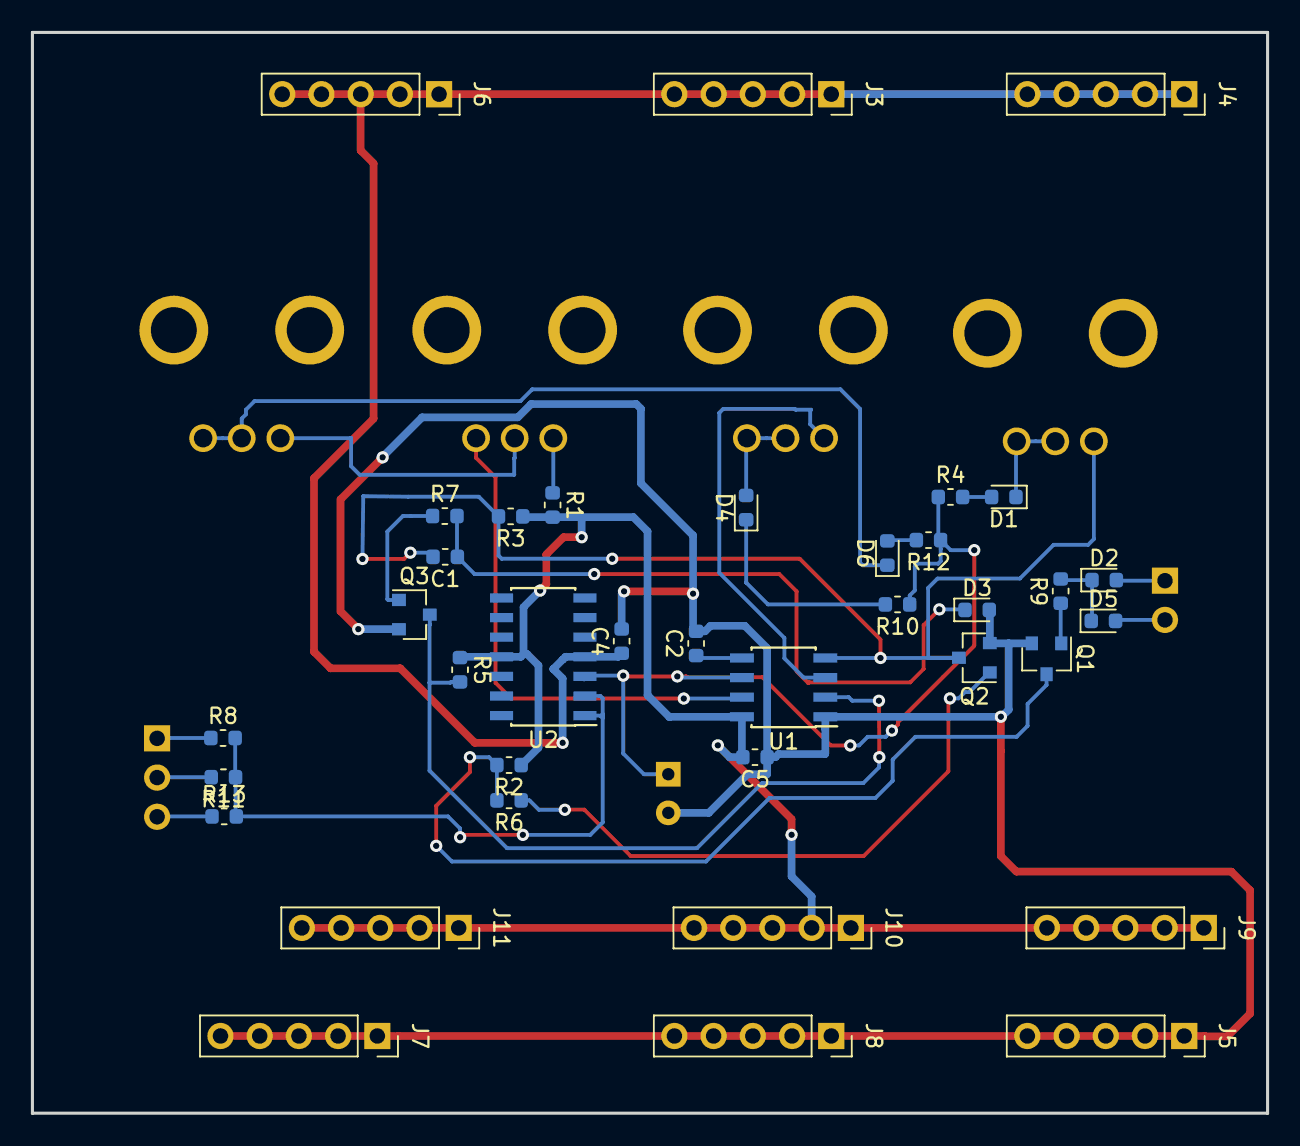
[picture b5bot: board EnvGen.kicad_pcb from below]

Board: 2 copper layers, 80.0 x 70.0 mm, 44 parts (37 on the bottom side), 29 nets.
